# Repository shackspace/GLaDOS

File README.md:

migrated to new location: https://codeberg.org/shackspace/GLaDOS

GLaDOS
======

artificial intelligence, sensors and pattering

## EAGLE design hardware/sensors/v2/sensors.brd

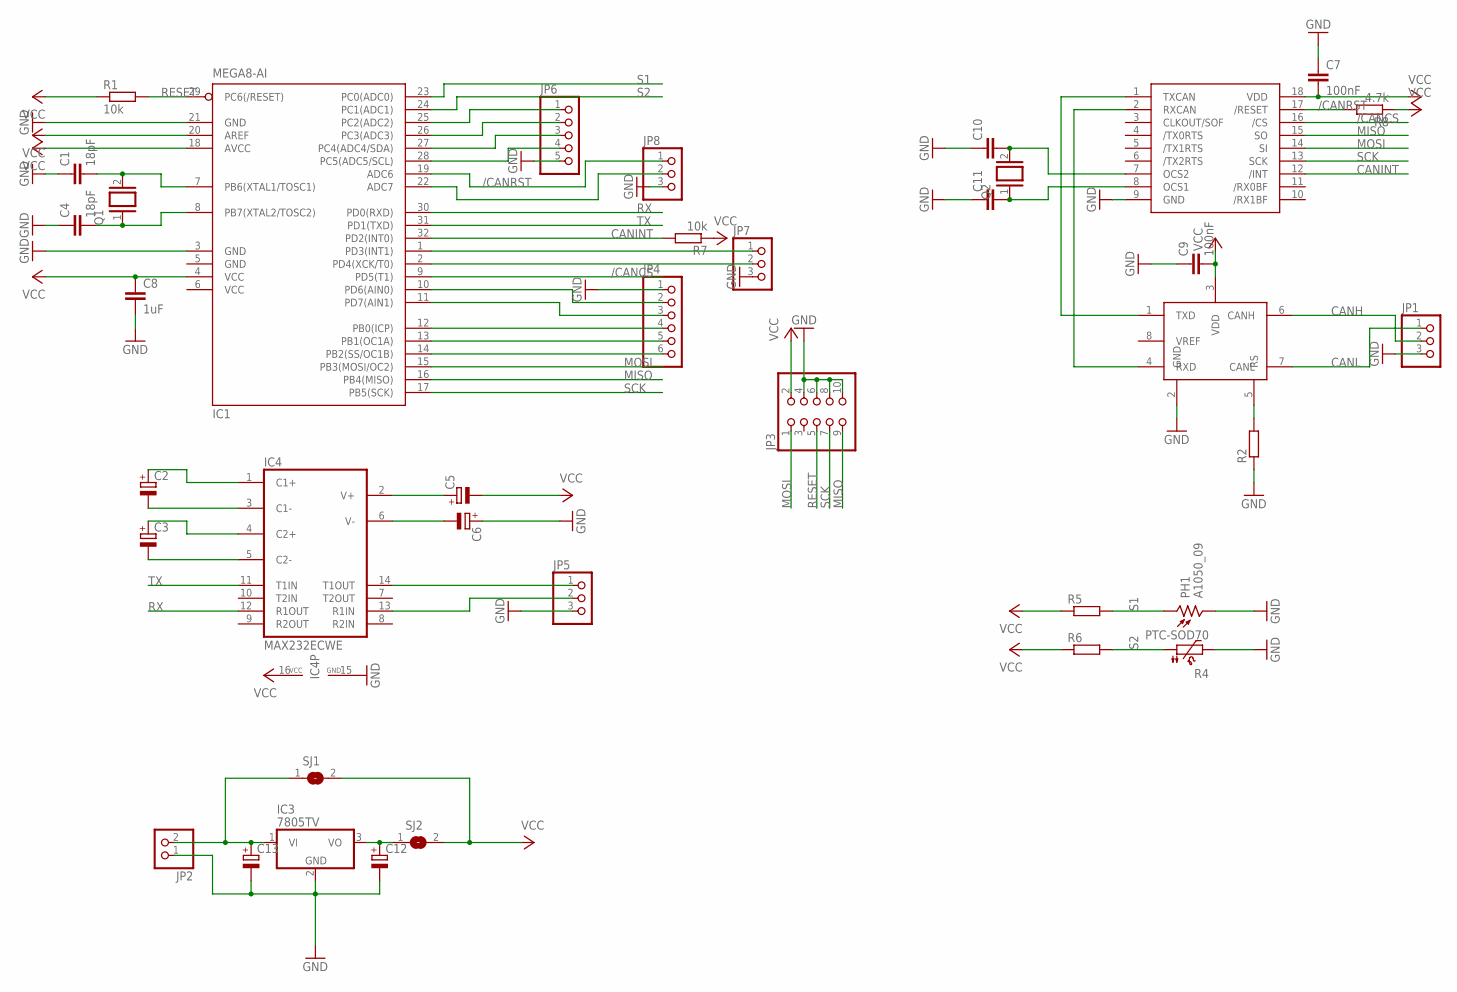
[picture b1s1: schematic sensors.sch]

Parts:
C1, C4: 18pF; C0805
C2, C3, C5, C6: CPOL-EUE3.5-8; E3,5-8
C7, C9: 100nF; C0603
C8: 1uF; C0603
C10, C11: C-EUC0805; C0805
C12, C13: CPOL-EU140CLH-0810; 140CLH-0810
IC1: MEGA8-AI; TQFP32-08
IC3: 7805TV; TO220V
IC4: MAX232ECWE; SO16L
JP1, JP5, JP7, JP8: PINHD-1X3; 1X03
JP2: PINHD-1X2; 1X02
JP3: PINHD-2X5; 2X05
JP4: PINHD-1X6; 1X06
JP6: PINHD-1X5; 1X05
PH1: A1050_09; T0-46-A10XX
Q1, Q2: XTAL/S; QS
R1, R7: 10k; R0805
R2, R5, R6: R-EU_R0805; R0805
R4: PTC-SOD70; SOD70
R8: 4.7k; R0805
SJ1, SJ2: SJ
U$1: MCP251518-LEAD_SOIC; SOIC18L
U$2: MCP2551SOIC8; SOIC8

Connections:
/CANCS: IC1.9 (PD5(T1)), U$1.16 (/CS)
/CANRST: IC1.19 (ADC6), JP8.1, R8.2, U$1.17 (/RESET)
CANH: JP1.2, U$2.6 (CANH)
CANINT: IC1.32 (PD2(INT0)), R7.2, U$1.12 (/INT)
CANL: JP1.1, U$2.7 (CANL)
GND: C1.1, C4.1, C6.+, C7.1, C8.2, C9.1, C10.1, C11.1, C12.-, C13.-, IC1.3 (GND), IC1.5 (GND), IC1.21 (GND), IC3.2 (GND), IC4.15 (GND), JP1.3, JP2.1, JP3.4, JP3.6, JP3.8, JP3.10, JP4.1, JP5.3, JP6.5, JP7.3, JP8.3, PH1.2, R2.1, R4.2, U$1.9 (GND), U$2.2 (GND)
MISO: IC1.16 (PB4(MISO)), JP3.9, U$1.15 (SO)
MOSI: IC1.15 (PB3(MOSI/OC2)), JP3.1, U$1.14 (SI)
unnamed: U$1.1 (TXCAN), U$2.1 (TXD)
unnamed: U$1.2 (RXCAN), U$2.4 (RXD)
unnamed: C3.+, IC4.4 (C2+)
unnamed: C2.-, IC4.3 (C1-)
unnamed: C2.+, IC4.1 (C1+)
unnamed: C3.-, IC4.5 (C2-)
unnamed: C1.2, IC1.7 (PB6(XTAL1/TOSC1)), Q1.2
unnamed: C4.2, IC1.8 (PB7(XTAL2/TOSC2)), Q1.1
unnamed: R2.2, U$2.5 (RS)
unnamed: IC4.14 (T1OUT), JP5.1
unnamed: IC4.13 (R1IN), JP5.2
unnamed: C5.+, IC4.2 (V+)
unnamed: C6.-, IC4.6 (V-)
unnamed: IC1.12 (PB0(ICP)), JP4.4
unnamed: C12.+, IC3.3 (VO), SJ2.1
unnamed: C13.+, IC3.1 (VI), JP2.2, SJ1.1
unnamed: IC1.13 (PB1(OC1A)), JP4.5
unnamed: IC1.14 (PB2(SS/OC1B)), JP4.6
unnamed: IC1.10 (PD6(AIN0)), JP4.2
unnamed: IC1.11 (PD7(AIN1)), JP4.3
unnamed: IC1.28 (PC5(ADC5/SCL)), JP6.4
unnamed: C10.2, Q2.2, U$1.7 (OCS2)
unnamed: IC1.27 (PC4(ADC4/SDA)), JP6.3
unnamed: IC1.26 (PC3(ADC3)), JP6.2
unnamed: IC1.25 (PC2(ADC2)), JP6.1
unnamed: IC1.1 (PD3(INT1)), JP7.1
unnamed: IC1.2 (PD4(XCK/T0)), JP7.2
unnamed: IC1.22 (ADC7), JP8.2
unnamed: C11.2, Q2.1, U$1.8 (OCS1)
RESET: IC1.29 (PC6(/RESET)), JP3.5, R1.2
RX: IC1.30 (PD0(RXD)), IC4.12 (R1OUT)
S1: IC1.23 (PC0(ADC0)), PH1.1, R5.2
S2: IC1.24 (PC1(ADC1)), R4.1, R6.2
SCK: IC1.17 (PB5(SCK)), JP3.7, U$1.13 (SCK)
TX: IC1.31 (PD1(TXD)), IC4.11 (T1IN)
VCC: C5.-, C7.2, C8.1, C9.2, IC1.4 (VCC), IC1.6 (VCC), IC1.18 (AVCC), IC1.20 (AREF), IC4.16 (VCC), JP3.2, R1.1, R5.1, R6.1, R7.1, R8.1, SJ1.2, SJ2.2, U$1.18 (VDD), U$2.3 (VDD)

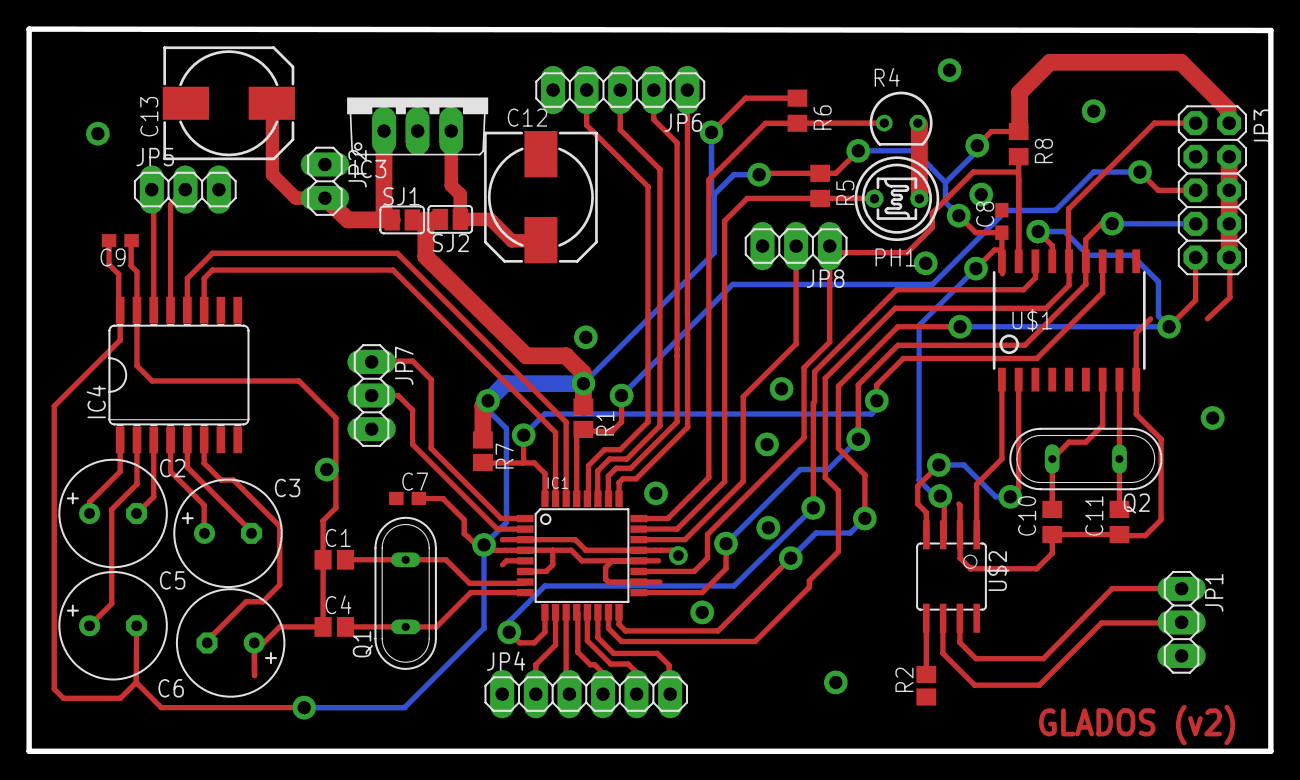
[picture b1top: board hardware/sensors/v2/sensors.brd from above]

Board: 2 copper layers, 93.9 x 54.6 mm, 38 parts (0 on the bottom side), 44 nets.

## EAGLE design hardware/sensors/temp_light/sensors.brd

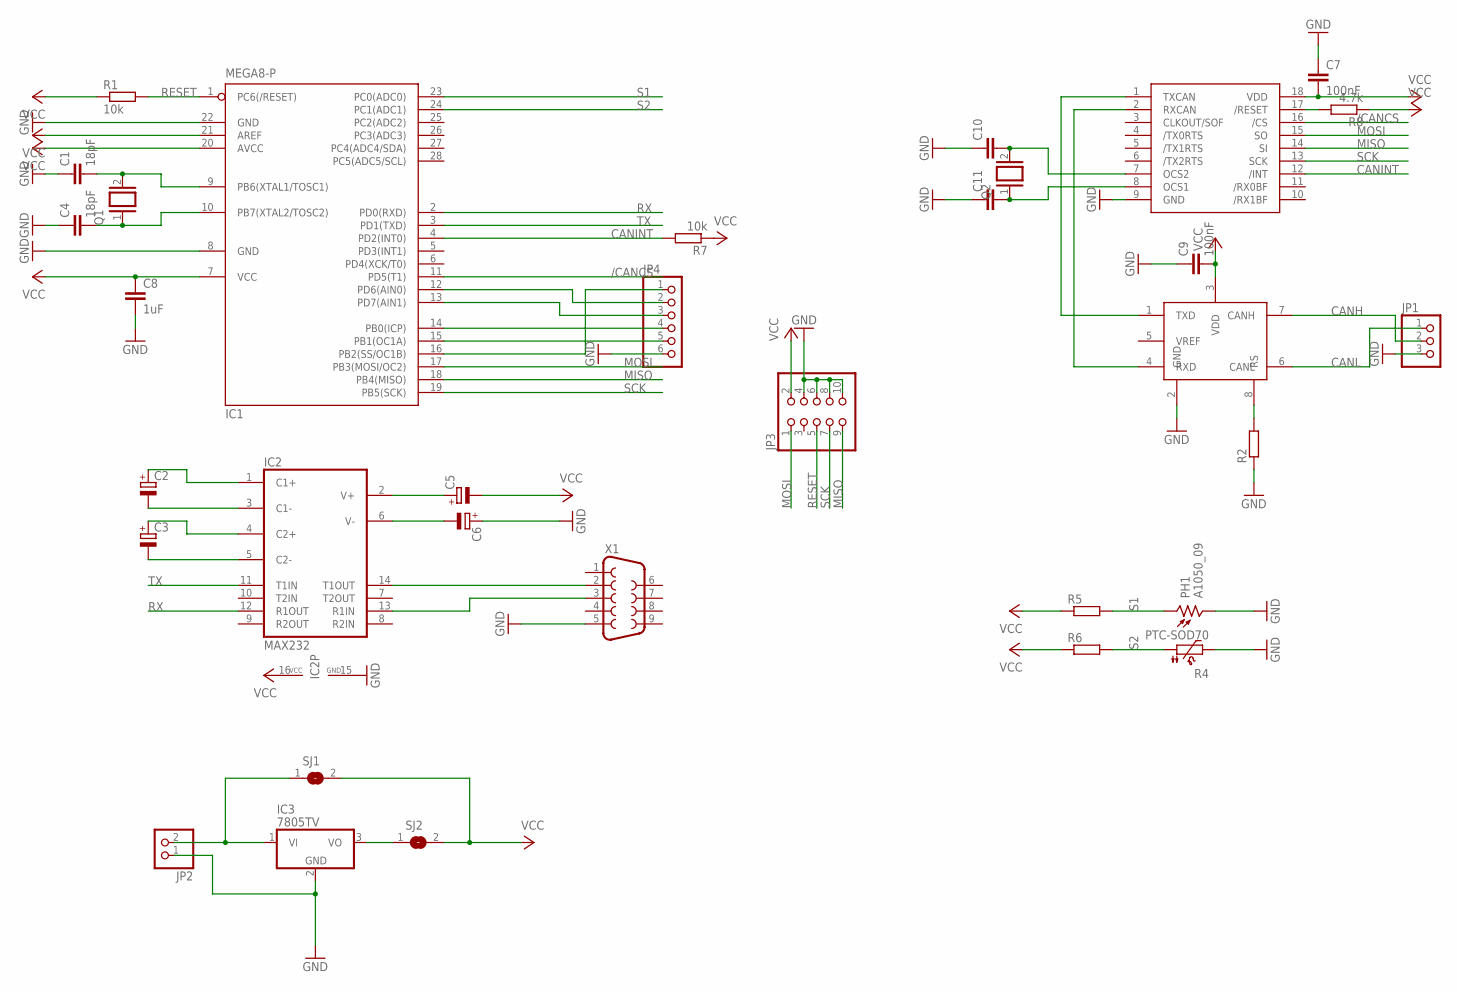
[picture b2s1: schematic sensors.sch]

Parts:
C1, C4: 18pF; C025-024X044
C2, C3, C5, C6: CPOL-EUE3.5-8; E3,5-8
C7, C9: 100nF; C0603
C8: 1uF; C0603
C10, C11: C-EUC0603; C0603
IC1: MEGA8-P; DIL28-3
IC2: MAX232; DIL16
IC3: 7805TV; TO220V
JP1: PINHD-1X3; 1X03
JP2: PINHD-1X2; 1X02
JP3: PINHD-2X5; 2X05
JP4: PINHD-1X6; 1X06
PH1: A1050_09; T0-46-A10XX
Q1, Q2: XTAL/S; QS
R1, R7: 10k; 0207/10
R2, R5, R6: R-EU_0207/10; 0207/10
R4: PTC-SOD70; SOD70
R8: 4.7k; 0207/10
SJ1, SJ2: SJ
U$1: MCP251518-LEAD_SOIC; SOIC18L
U$2: MCP2551DIL8; DIL8
X1: F09HP

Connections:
/CANCS: IC1.11 (PD5(T1)), U$1.16 (/CS)
CANH: JP1.2, U$2.7 (CANH)
CANINT: IC1.4 (PD2(INT0)), R7.2, U$1.12 (/INT)
CANL: JP1.1, U$2.6 (CANL)
GND: C1.1, C4.1, C6.+, C7.1, C8.2, C9.1, C10.1, C11.1, IC1.8 (GND), IC1.22 (GND), IC2.15 (GND), IC3.2 (GND), JP1.3, JP2.1, JP3.4, JP3.6, JP3.8, JP3.10, JP4.6, PH1.2, R2.1, R4.2, U$1.9 (GND), U$2.2 (GND), X1.5
MISO: IC1.18 (PB4(MISO)), JP3.9, U$1.14 (SI)
MOSI: IC1.17 (PB3(MOSI/OC2)), JP3.1, U$1.15 (SO)
unnamed: U$1.1 (TXCAN), U$2.1 (TXD)
unnamed: U$1.2 (RXCAN), U$2.4 (RXD)
unnamed: C3.+, IC2.4 (C2+)
unnamed: C2.-, IC2.3 (C1-)
unnamed: C2.+, IC2.1 (C1+)
unnamed: C3.-, IC2.5 (C2-)
unnamed: C1.2, IC1.9 (PB6(XTAL1/TOSC1)), Q1.2
unnamed: C4.2, IC1.10 (PB7(XTAL2/TOSC2)), Q1.1
unnamed: R2.2, U$2.8 (RS)
unnamed: IC2.14 (T1OUT), X1.2
unnamed: IC2.13 (R1IN), X1.3
unnamed: C5.+, IC2.2 (V+)
unnamed: C6.-, IC2.6 (V-)
unnamed: IC1.14 (PB0(ICP)), JP4.4
unnamed: IC3.3 (VO), SJ2.1
unnamed: IC3.1 (VI), JP2.2, SJ1.1
unnamed: IC1.15 (PB1(OC1A)), JP4.5
unnamed: IC1.16 (PB2(SS/OC1B)), JP4.1
unnamed: IC1.12 (PD6(AIN0)), JP4.2
unnamed: IC1.13 (PD7(AIN1)), JP4.3
unnamed: R8.2, U$1.17 (/RESET)
unnamed: C10.2, Q2.2, U$1.7 (OCS2)
unnamed: C11.2, Q2.1, U$1.8 (OCS1)
RESET: IC1.1 (PC6(/RESET)), JP3.5, R1.2
RX: IC1.2 (PD0(RXD)), IC2.12 (R1OUT)
S1: IC1.23 (PC0(ADC0)), PH1.1, R5.2
S2: IC1.24 (PC1(ADC1)), R4.1, R6.2
SCK: IC1.19 (PB5(SCK)), JP3.7, U$1.13 (SCK)
TX: IC1.3 (PD1(TXD)), IC2.11 (T1IN)
VCC: C5.-, C7.2, C8.1, C9.2, IC1.7 (VCC), IC1.20 (AVCC), IC1.21 (AREF), IC2.16 (VCC), JP3.2, R1.1, R5.1, R6.1, R7.1, R8.1, SJ1.2, SJ2.2, U$1.18 (VDD), U$2.3 (VDD)

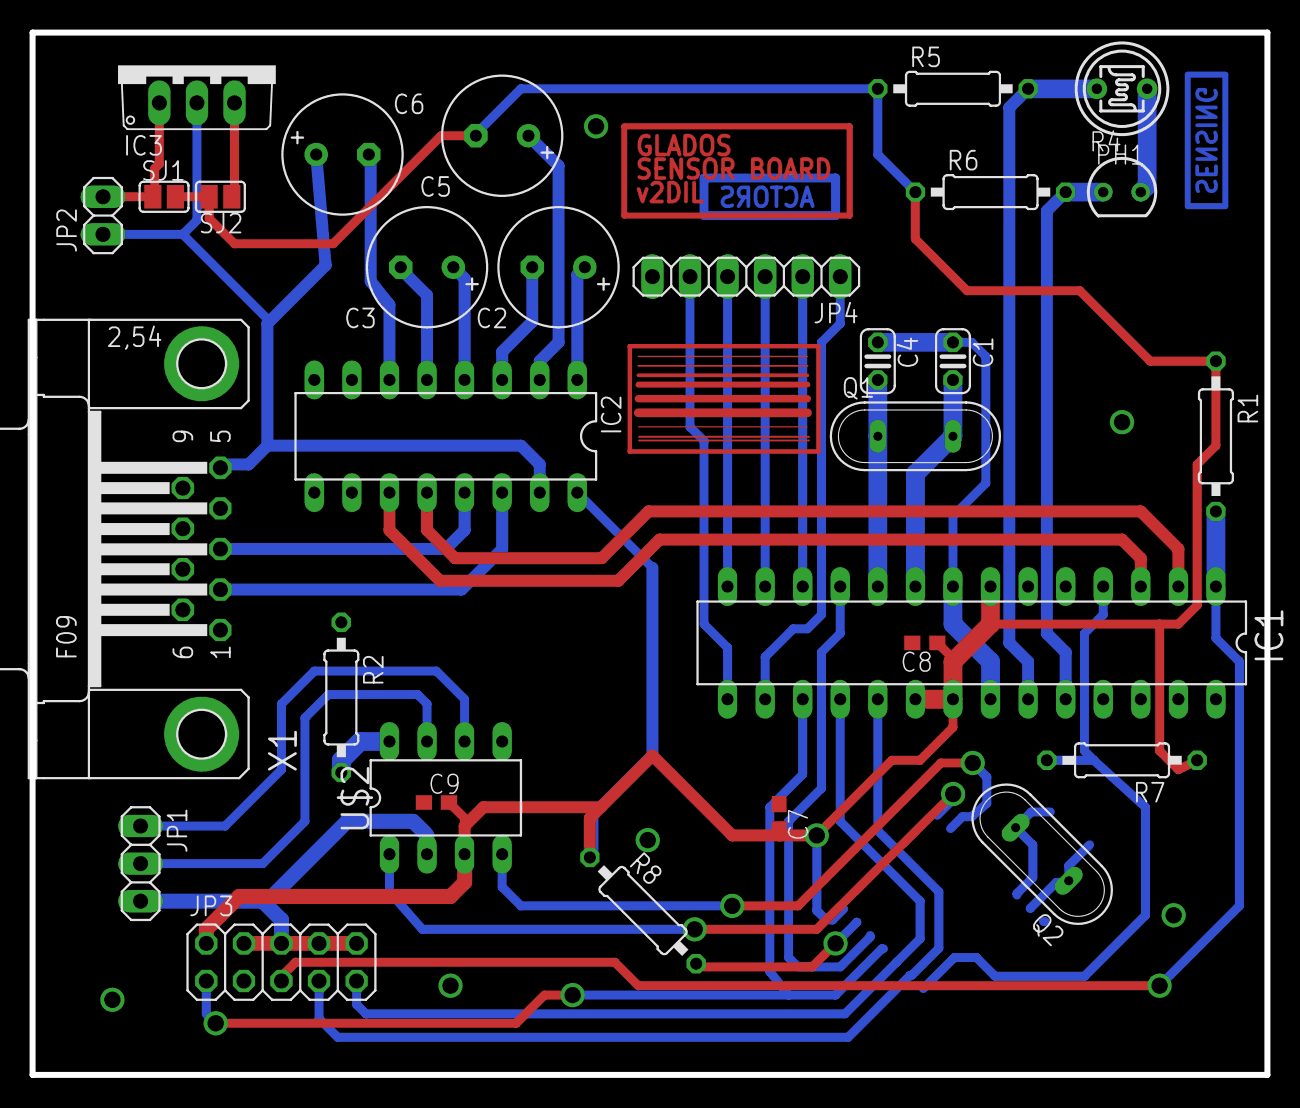
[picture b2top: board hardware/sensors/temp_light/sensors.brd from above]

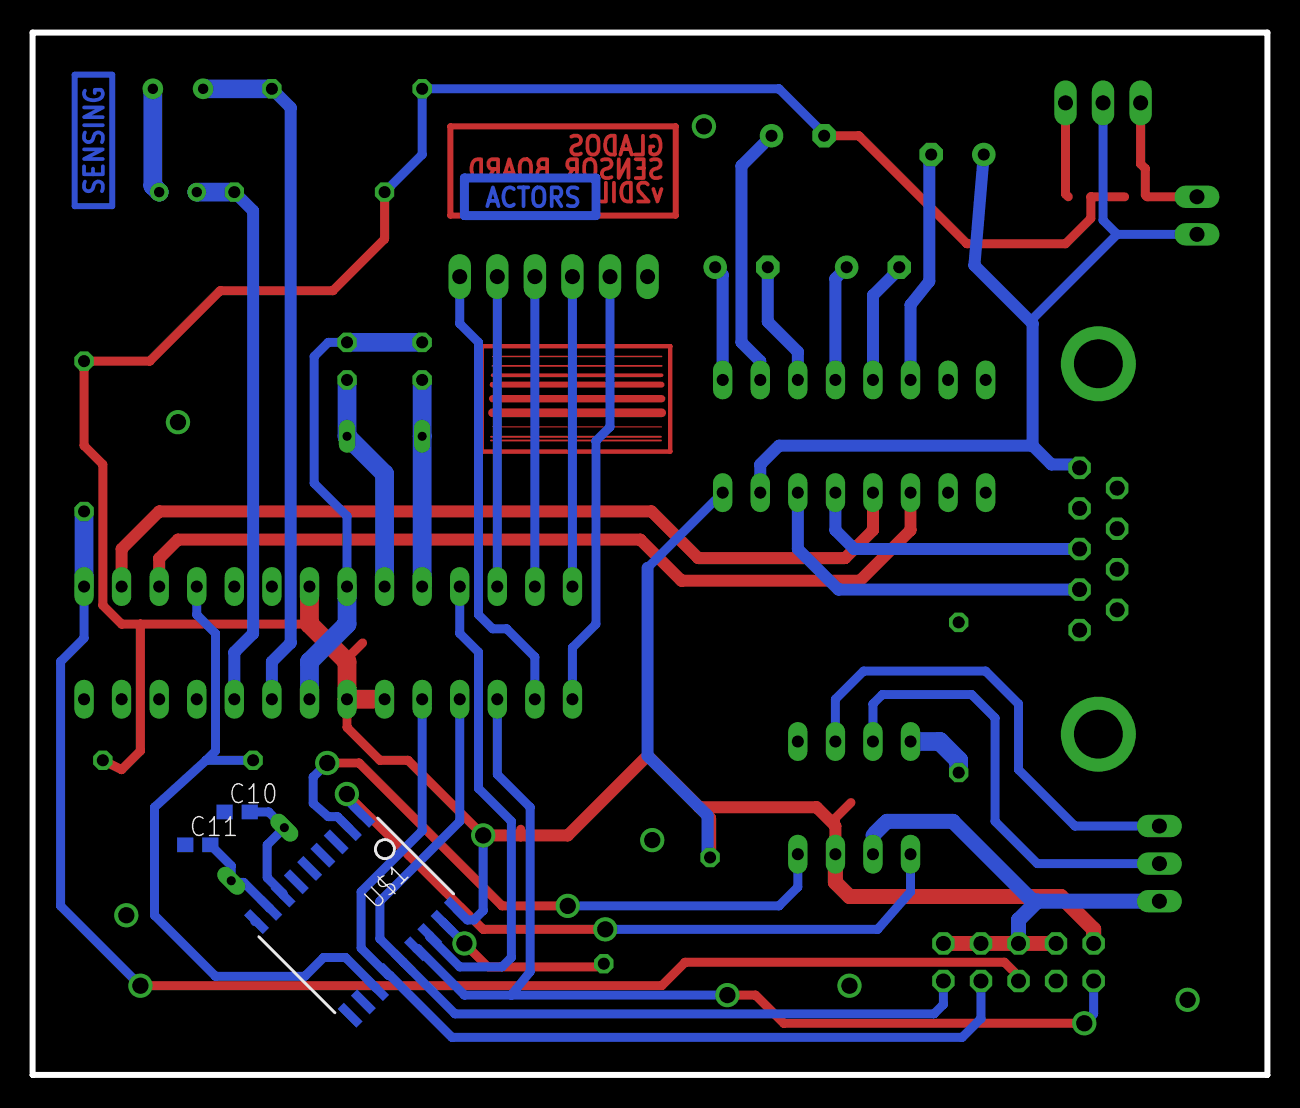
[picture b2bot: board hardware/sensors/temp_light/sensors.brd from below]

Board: 2 copper layers, 83.5 x 70.5 mm, 33 parts (3 on the bottom side), 37 nets.

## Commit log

2012-08-12 added schematics and board files for sensor prototypes
2012-08-13 added glados base library
2012-08-13 added parts of firmware for glados sensor boards
2012-08-15 changes to fix a bug in the hardware and make it DRC proof
2012-08-16 working some more on the firmware
2012-08-19 added bugfix to firmware, added code for sending a can message with values
2013-02-08 inital commit for the power monitor
2013-02-11 reads out all the power meters
2013-02-11 can now send the data to a redis database and uses the data format from the redis-schema.md / github.com/hdznrrd/siid-doc/database
2013-02-11 adds json configuration object for the power sensor
2013-02-11 use lists instead of sets for storing the data in the redis db
2013-02-11 the values are now trimmed to remove leading zeros.
2013-02-11 cleanup
2013-02-13 set lights
2013-02-13 added light monitor that will sample the light on / off values to redis
2013-02-13 output messages
2013-02-15 implemented another method of measuring power using watchasync from ehtersex
2013-02-23 collectors will now reconnect to redis on connection loss
2013-02-23 uses local time in milliseconds
2026-06-10 add migration note
2026-06-10 undo migration note
